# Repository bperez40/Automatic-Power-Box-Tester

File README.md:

# Automatic Power Box Tester
Summer 2022 ITW Vulcan Project

## Firmware Guide
 This guide assumes you're running Windows, however, you can easily do all this on other platforms, but some of the steps will vary slightly, and you probably won't be using anything with a batch script on another platform (unless you really want to).

### Cloning Repo (required)
If you don't have git installed, go ahead and download it from here: https://git-scm.com/
Then, in a command-line shell (On Windows, Command Prompt and PowerShell are installed by default), navigate to wherever you want to store the project and then run:
git clone https://github.com/bperez40/Arduino-Power-Box-Tester

The repository is layed out as follows
```
Automatic-Power-Box-Tester
├───lib
│   ├───Adafruit-GFX-Library
│   ├───Adafruit_BusIO
│   ├───Adafruit_RA8875
│   ├───iodefs
│   ├───PBTCheck
│   ├───PBTGraphics
│   └───PWM
├───main
├───tests
│   ├───ADC_test
│   └───PWM_Out
└───util
    ├───Hardware Design Files
    │   ├───AutoPowerBoxTesterv1.0
    │   │   └───GerberFiles
    │   ├───AutoPowerBoxTesterv1.1
    │   │   └───GerberFiles
    │   └───SparkWireInterfacev1.0
    │       └───GerberFiles
    ├───scripts
    └───images
```
Opening it up, you'll be on the root of the repository.
- main stores the main program
- lib has all the required external and custom libraries for the project
- tests has some basic tests mostly used for debugging and not much else
- util has images used in the readme as well as all the hardware design files for the PCBs

Go ahead and run the update.bat script. This initializes all the submodules, which have dependencies that the firmware uses. Also run this whenever you want to pull the most recent version of the firmware.

### Arduino Setup (required)
We're not quite ready to actually compile and upload firmware to the Arduino yet. We need to install a program to do so. You have a few ways to do this.

#### 1. Using Arduino CLI (recommended)
If you want to use the Arduino CLI to make your own custom configuration, start by downloading the Arduino CLI from Arduino here: https://www.arduino.cc/pro/cli

Extract it in the repository's root and rename the folder it's contained in to .arduino-cli. So, {top-of-repository}/.arduino-cli

Your new file structure will look something like this...
```
Automatic-Power-Box-Tester
├───.arduino-cli
├───lib
│   ├───Adafruit-GFX-Library
│   ├───Adafruit_BusIO
│   ├───Adafruit_RA8875
│   ├───iodefs
│   ├───PBTCheck
│   ├───PBTGraphics
│   └───PWM
├───main
├───tests
│   ├───ADC_test
│   └───PWM_Out
└───util
    ├───Hardware Design Files
    │   ├───AutoPowerBoxTesterv1.0
    │   │   └───GerberFiles
    │   ├───AutoPowerBoxTesterv1.1
    │   │   └───GerberFiles
    │   └───SparkWireInterfacev1.0
    │       └───GerberFiles
    ├───scripts
    └───images
```

The fast way to compile and upload the program is to run the CompileAndUpload.bat script in util.

If you want to compile it manually and play around the the CLI a bit, you can do the following.

To compile, run the following from your root folder:

arduino-cli.exe compile --build-path ./build --libraries ./lib -b Arduino:avr:mega main/main.ino

To compile and upload, you can instead do:

arduino-cli.exe compile --build-path ./build --libraries ./lib -b Arduino:avr:mega -p COM4 -u main/main.ino

Replacing COM4 with whatever your Arduino is actually using. You can figure that out by running:

arduino-cli.exe board list

This is also how you can figure out an Arduino's FQBN.

#### 2. Using Arduino IDE
I haven't set this up on Arduino IDE, but I imagine this is what people are more familar with when using any Arduino platform. If you do this, you'll have to manually add the libraries using the GUI and set up the board type and COM port similar to option 2. If that's done correctly, all you have to do is press the run button and it should work fine.

### Changing the lock screen password (important, but optional)
I recognize that this is incredibly insecure, but it's highly unlikely anyone who would abuse this would come looking here to do so.

To change the lockscreen password, navigate to PBTGraphics.cpp and change the line with...

int actual_passcode[4] = {#, #, #, #}; /*!! SET PASSCODE HERE !!*/

...by setting the # to whatever you want it to be, in the order you want them to be entered. Then build and upload the project to the Arduino.

### Running Python Scripts (optional)
If you don't already have it installed, install from their website: https://www.python.org/

Once Python is installed, open a terminal. 

In the repository's root folder, run python -m venv .venv
.venv is gitignored by default, but if you want to name it something else, change the gitignore to reflect whatever you call it.

VSCode should give a prompt that it has detected a new virtual environment. Confirm the prompt.

Select the proper virtual environment interpreter by opening the command pallette and selecting it using >Python: Select Interpreter

In Windows, run the activate script to use your virtual environment. You could use the
global environment instead, but that's icky:
{wherever-venv-is}\.venv\scripts\activate

If using the debugger, you might need to activate it again in the new terminal that pops up.

If you get the message "Activate.ps1" is not digitally signed, run:
Set-ExecutionPolicy -ExecutionPolicy RemoteSigned -Scope Process

Once the virtual environment is activated, install whatever packages you want using
pip install {package-name}
If you get an error running a python script, chances are you're missing a package. Read the terminal output to see what exactly the error is.

Whenever you're done working in the virtual environment, type deactivate and you'll leave the virtual environment and return to the global environment.

### Logging Arduino output data using PuTTY (optional)
If you want to log the Arduino's output data when it's connected over USB, you can do so using PuTTY (or TeraTerm, or whatever other similar program).

First, install PuTTY from here: https://www.putty.org/

Match all the proper settings in the session tab, such as COM port, baud rate, so on so forth.

In the logging tab, set session logging to "All session output." Name the file whatever you like and configure PuTTY to store putty.log or whatever you want to call it in the util folder of the repository. When you start a session, PuTTY will then create a log in the util folder. You can run the visualizer python script to then visualize the file's output. This is useful for graphing ADC data.

If you want to start PuTTY using a terminal, run the following command:

plink.exe -load {SAVED-PROFILE}

Where the saved profile is one that you've previously set up. If plink.exe isn't found, make sure it's part of your PATH environment.

## Hardware
Hardware design files and assembly instructions can be found in util/HardwareDesignFiles.\
They include the EAGLE board and schematic files, gerber files, BOM, and pick and place for each board.\
You can also view each board on AISLER with the following links.\
[Auto Power Box Tester v1.1 (redirect)](https://aisler.net/p/JCLNWTRR)\
[Spark Wire Interface Board v1.0 (redirect)](https://aisler.net/p/PQONZLWA)\
[Auto Power Box Tester v1.0 (redirect)](https://aisler.net/p/SKLRNZQZ)

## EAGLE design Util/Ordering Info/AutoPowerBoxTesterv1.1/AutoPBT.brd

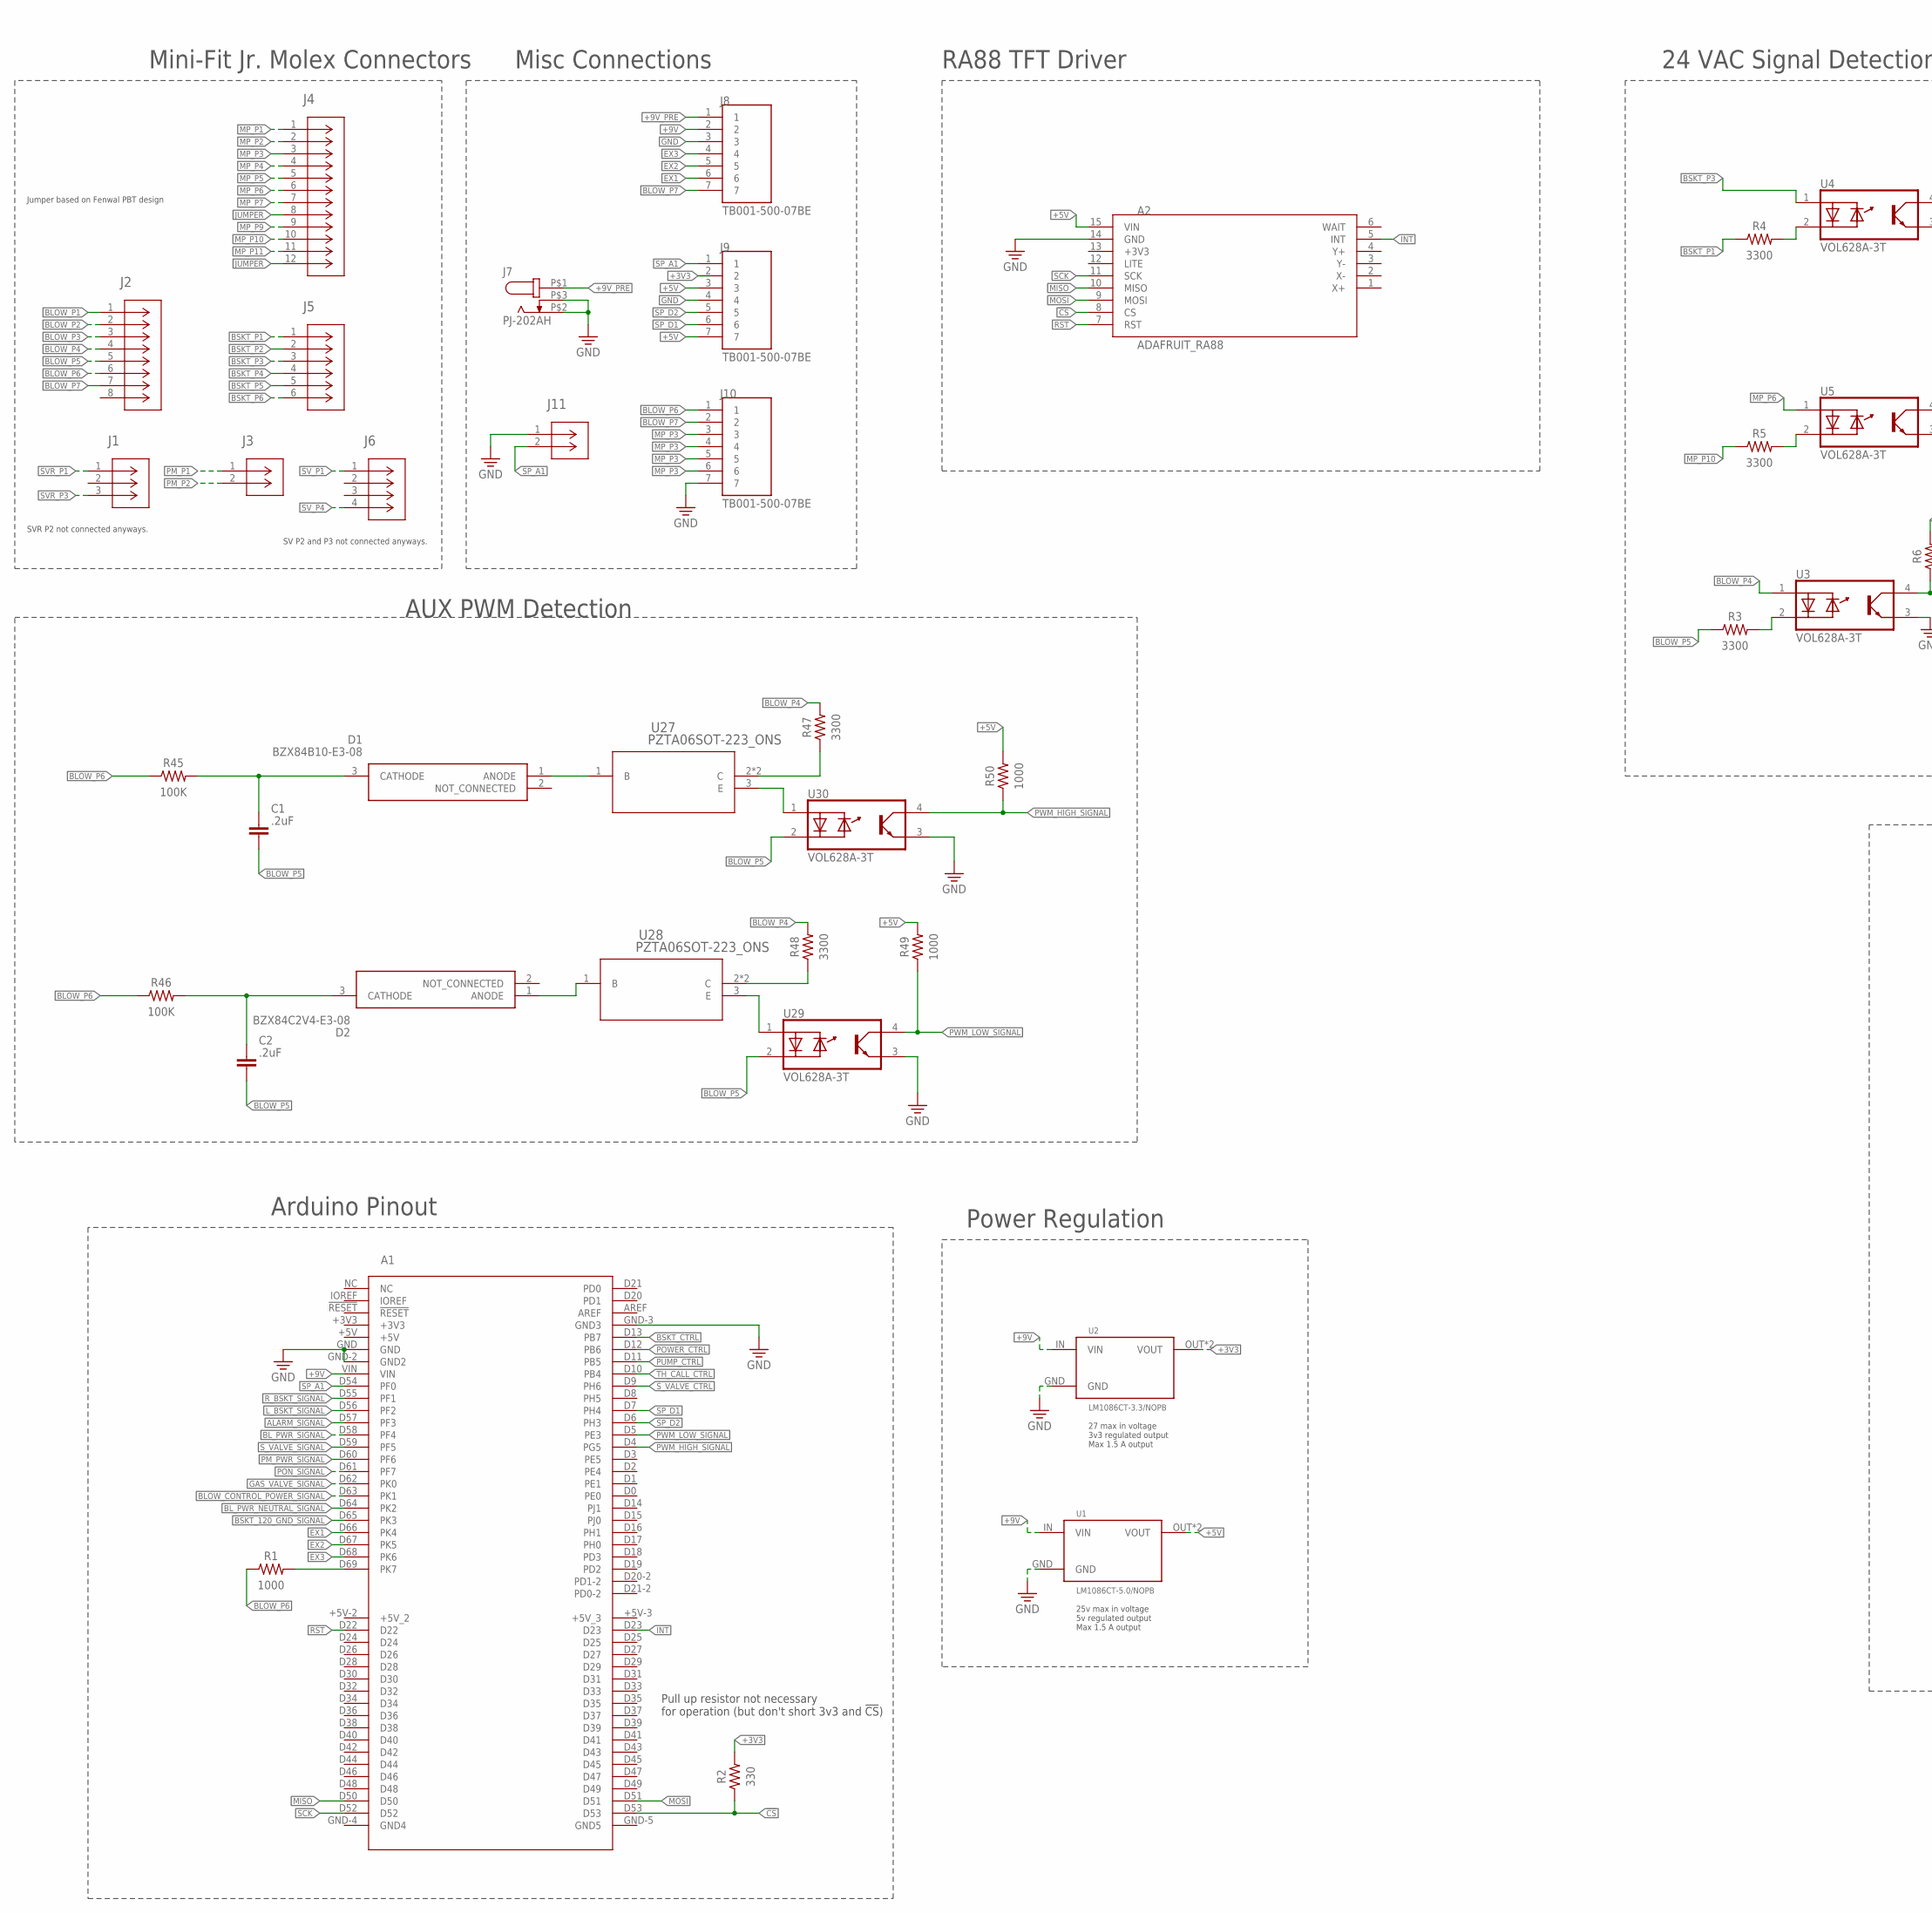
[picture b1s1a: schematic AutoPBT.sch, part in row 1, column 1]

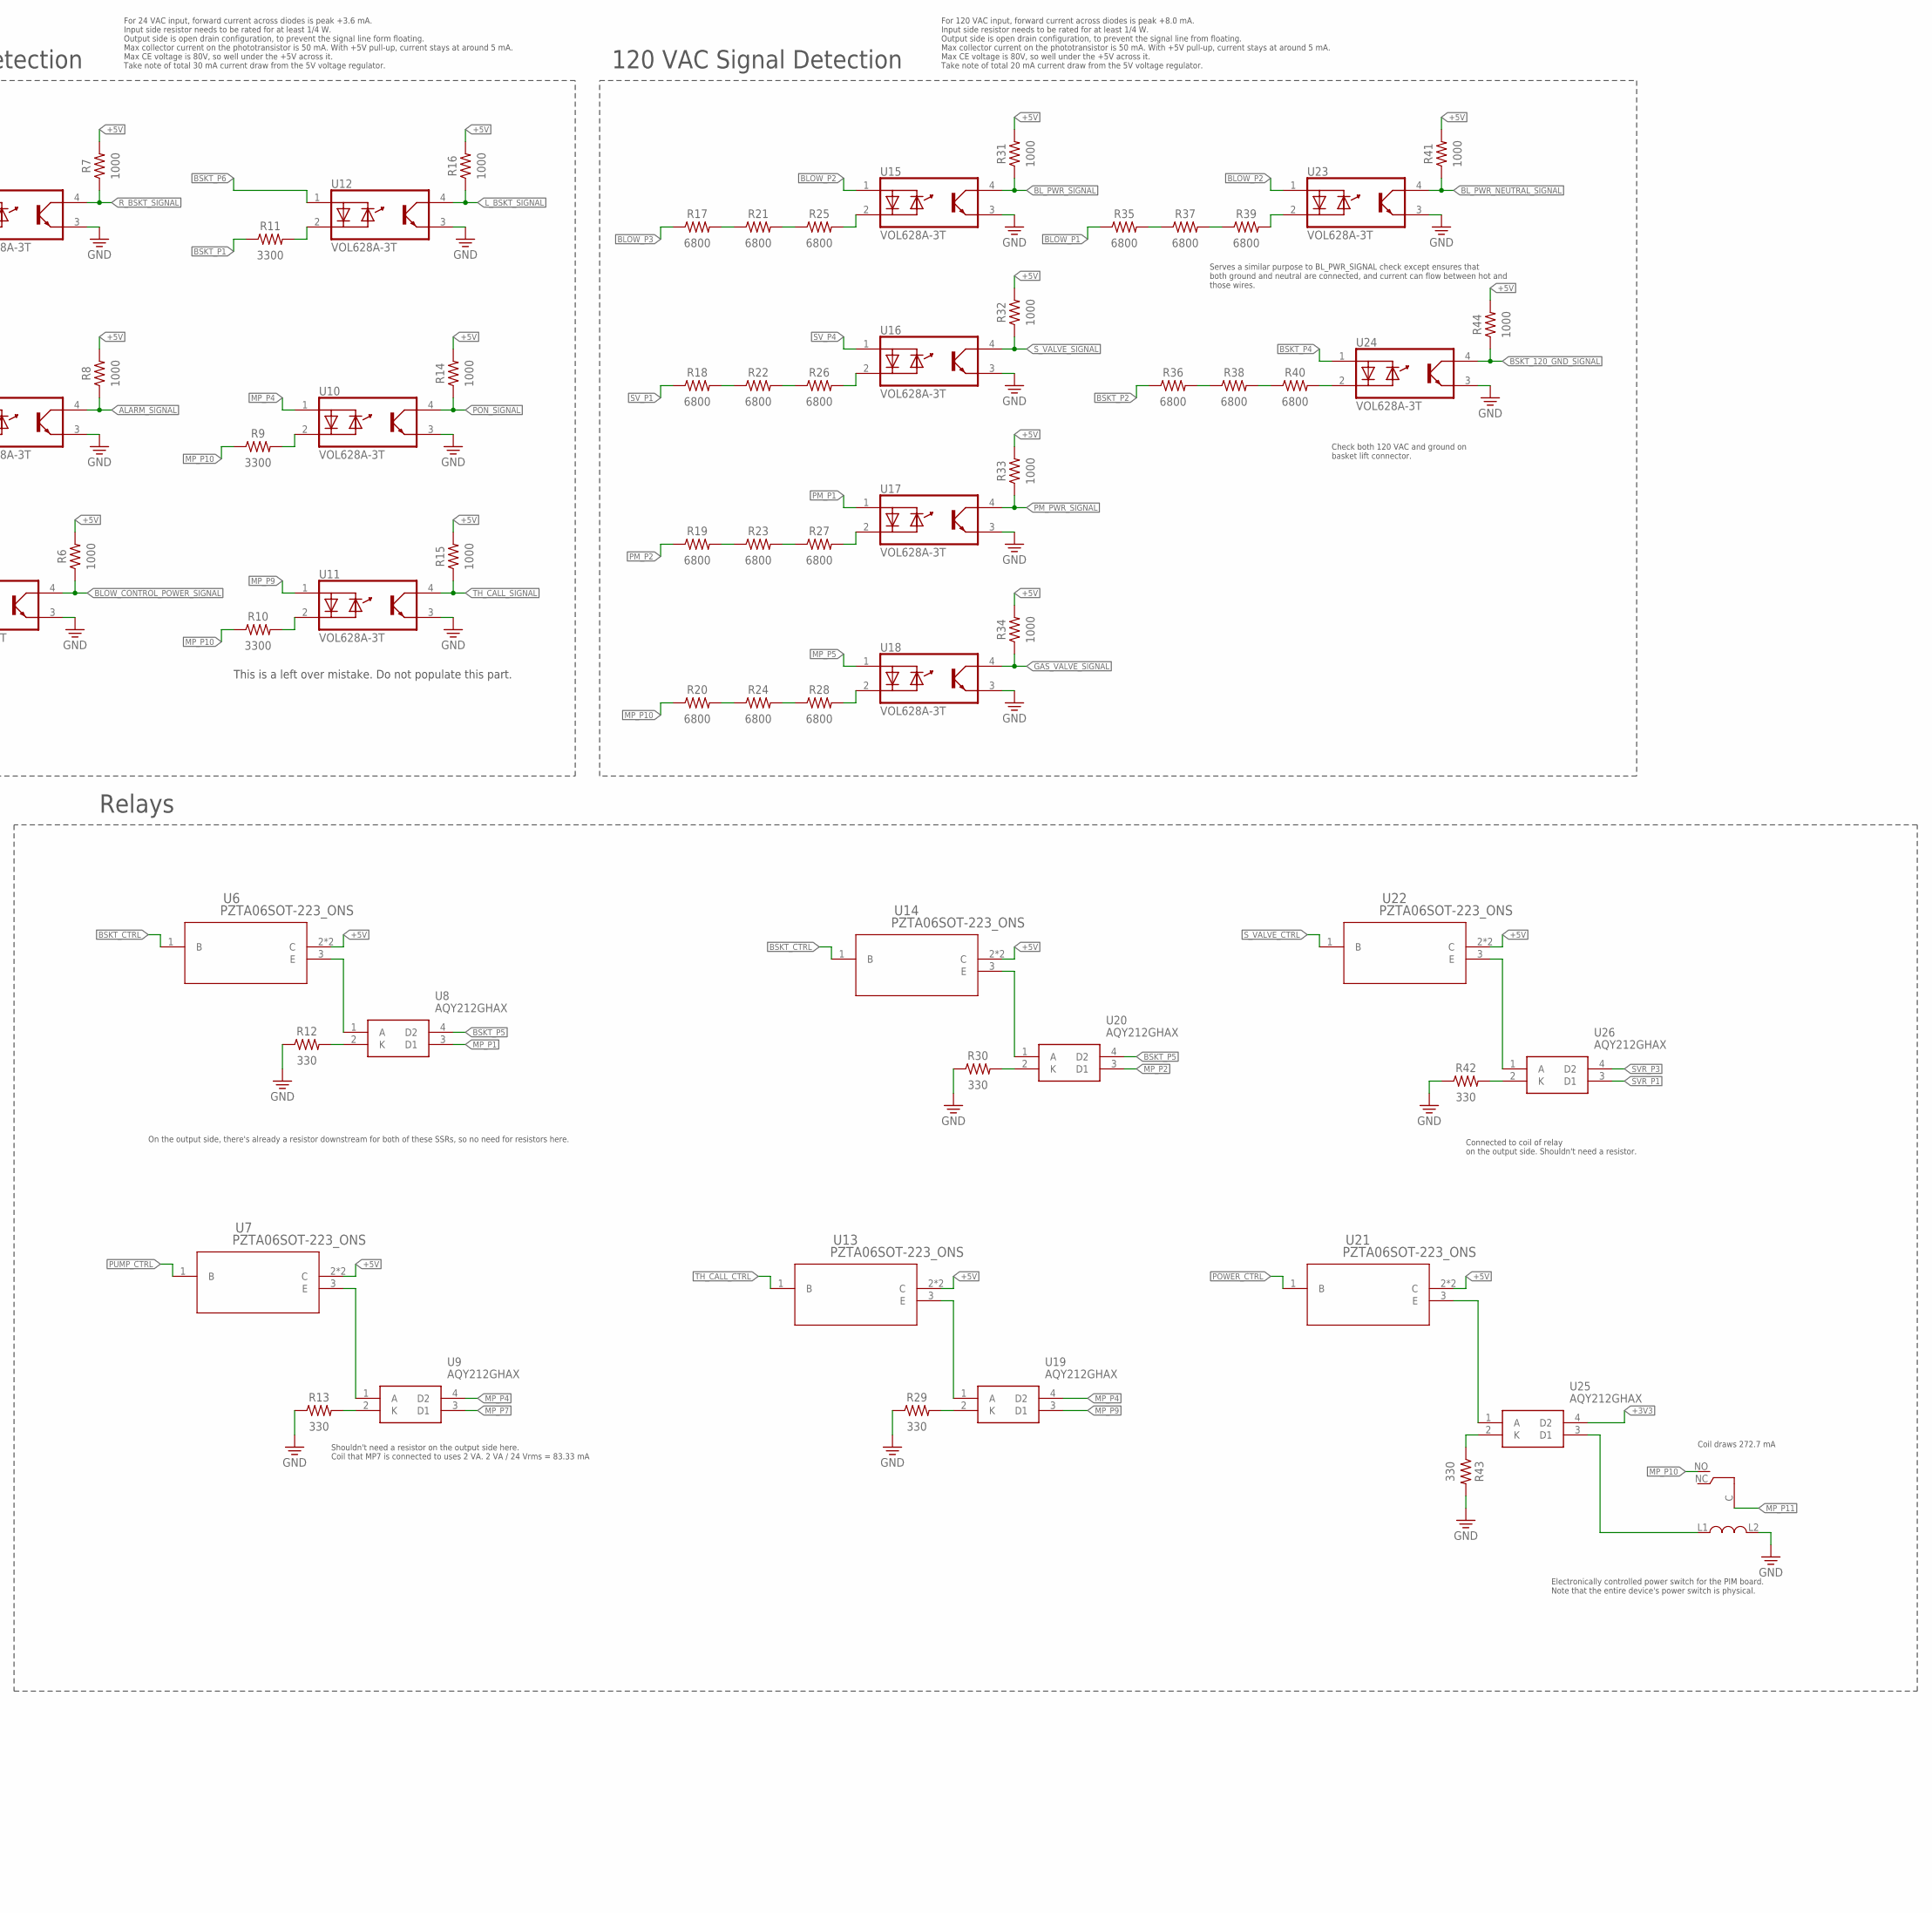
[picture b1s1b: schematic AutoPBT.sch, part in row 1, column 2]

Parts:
A1: ARDUINO2560ARDUINO2560ACTUAL; ARDUINO2560PINS
A2: ADAFRUIT_RA88; RA88
C1, C2: .2uF; CAPC1608X85
D1: BZX84B10-E3-08; SOT95P248X115-3N
D2: BZX84C2V4-E3-08; SOT95P248X115-3N
J1: 39301039CON_39301039; CON_39301039
J2: 39281083CON_39281083; CON_39281083
J3: 39281023CON_39281023; CON_39281023
J4: 39281123CON_39281123; CON_39281123
J5: 39281063CON_39281063; CON_39281063
J6: 39299046CON_39299046; CON_39299046
J7: PJ-202AH; CUI_PJ-202AH
J8, J9, J10: TB001-500-07BE; CUI_TB001-500-07BE
J11: 430450212CON_430450212_MOL; CON_430450212_MOL
K1: J107F1CS203VDC.80
R1, R6, R7, R8, R14, R15, R16, R31, R32, R33, R34, R41, R44, R49, R50: 1000; RESC1608X60
R2, R12, R13, R29, R30, R42, R43: 330; RESC1608X60
R3, R4, R5, R9, R10, R11, R47, R48: 3300; RESC1608X60
R17, R18, R19, R20, R21, R22, R23, R24, R25, R26, R27, R28, R35, R36, R37, R38, R39, R40: 6800; RESC1608X60
R45, R46: 100K; RESC1608X60
U1: LM1086CT-5.0/NOPB; LM1086CT-3.3/NOPB
U2: LM1086CT-3.3/NOPB
U3, U4, U5, U10, U11, U12, U15, U16, U17, U18, U23, U24, U29, U30: VOL628A-3T; SOIC254P1020X230-4N
U6, U7, U13, U14, U21, U22, U27, U28: PZTA06SOT-223_ONS; SOT-223_ONS
U8, U9, U19, U20, U25, U26: AQY212GHAX; SOP254P962X315-4N

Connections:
!CS!: A1.D53, A2.8 (CS), R2.1
+3V3: J9.2, R2.2, U2.OUT (VOUT), U2.OUT2 (VOUT), U25.4 (D2)
+5V: A2.15 (VIN), J9.3, J9.7, R6.2, R7.2, R8.2, R14.2, R15.2, R16.2, R31.2, R32.2, R33.2, R34.2, R41.2, R44.2, R49.2, R50.2, U1.OUT (VOUT), U1.OUT2 (VOUT), U6.2 (C), U6.4 (C), U7.2 (C), U7.4 (C), U13.2 (C), U13.4 (C), U14.2 (C), U14.4 (C), U21.2 (C), U21.4 (C), U22.2 (C), U22.4 (C)
+9V: A1.VIN, J8.2, U1.IN (VIN), U2.IN (VIN)
+9V_PRE: J7.P$1 (1), J8.1
ALARM_SIGNAL: A1.D57 (PF3), R8.1, U5.4 (CO)
BLOW_CONTROL_POWER_SIGNAL: A1.D63 (PK1), R6.1, U3.4 (CO)
BLOW_P1: J2.1, R35.1
BLOW_P2: J2.2, U15.1 (A/C), U23.1 (A/C)
BLOW_P3: J2.3, R17.1
BLOW_P4: J2.4, R47.2, R48.2, U3.1 (A/C)
BLOW_P5: C1.2, C2.2, J2.5, R3.1, U29.2 (C/A), U30.2 (C/A)
BLOW_P6: J2.6, J10.1, R1.1, R45.1, R46.1
BLOW_P7: J2.7, J8.7, J10.2
BL_PWR_NEUTRAL_SIGNAL: A1.D64 (PK2), R41.1, U23.4 (CO)
BL_PWR_SIGNAL: A1.D58 (PF4), R31.1, U15.4 (CO)
BSKT_120_GND_SIGNAL: A1.D65 (PK3), R44.1, U24.4 (CO)
BSKT_CTRL: A1.D13 (PB7), U6.1 (B), U14.1 (B)
BSKT_P1: J5.1, R4.1, R11.1
BSKT_P2: J5.2, R36.1
BSKT_P3: J5.3, U4.1 (A/C)
BSKT_P4: J5.4, U24.1 (A/C)
BSKT_P5: J5.5, U8.4 (D2), U20.4 (D2)
BSKT_P6: J5.6, U12.1 (A/C)
EX1: A1.D66 (PK4), J8.6
EX2: A1.D67 (PK5), J8.5
EX3: A1.D68 (PK6), J8.4
GAS_VALVE_SIGNAL: A1.D62 (PK0), R34.1, U18.4 (CO)
GND: A1.GND, A1.GND-2 (GND2), A1.GND-3 (GND3), A2.14 (GND), J7.P$2 (2), J7.P$3 (3), J8.3, J9.4, J10.7, J11.1, K1.L2 (5), R12.1, R13.1, R29.1, R30.1, R42.1, R43.2, U1.GND, U2.GND, U3.3 (E), U4.3 (E), U5.3 (E), U10.3 (E), U11.3 (E), U12.3 (E), U15.3 (E), U16.3 (E), U17.3 (E), U18.3 (E), U23.3 (E), U24.3 (E), U29.3 (E), U30.3 (E)
INT: A1.D23, A2.5 (INT)
JUMPER: J4.8, J4.12
L_BSKT_SIGNAL: A1.D56 (PF2), R16.1, U12.4 (CO)
MISO: A1.D50, A2.10 (MISO)
MOSI: A1.D51, A2.9 (MOSI)
MP_P1: J4.1, U8.3 (D1)
MP_P2: J4.2, U20.3 (D1)
MP_P3: J4.3, J10.3, J10.4, J10.5, J10.6
MP_P4: J4.4, U9.4 (D2), U10.1 (A/C), U19.4 (D2)
MP_P5: J4.5, U18.1 (A/C)
MP_P6: J4.6, U5.1 (A/C)
MP_P7: J4.7, U9.3 (D1)
MP_P9: J4.9, U11.1 (A/C), U19.3 (D1)
MP_P10: J4.10, K1.NO (1), R5.1, R9.1, R10.1, R20.1
MP_P11: J4.11, K1.C (3)
unnamed: R30.2, U20.2 (K)
unnamed: R29.2, U19.2 (K)
unnamed: R13.2, U9.2 (K)
unnamed: U6.3 (E), U8.1 (A)
unnamed: R42.2, U26.2 (K)
unnamed: R43.1, U25.2 (K)
unnamed: U14.3 (E), U20.1 (A)
unnamed: R39.2, U23.2 (C/A)
unnamed: R37.2, R39.1
unnamed: R35.2, R37.1
unnamed: R40.2, U24.2 (C/A)
unnamed: R38.2, R40.1
unnamed: R36.2, R38.1
unnamed: U22.3 (E), U26.1 (A)
unnamed: U7.3 (E), U9.1 (A)
unnamed: R9.2, U10.2 (C/A)
unnamed: U13.3 (E), U19.1 (A)
unnamed: U21.3 (E), U25.1 (A)
unnamed: R11.2, U12.2 (C/A)
unnamed: C2.1, D2.3 (CATHODE), R46.2
unnamed: R3.2, U3.2 (C/A)
unnamed: R4.2, U4.2 (C/A)
unnamed: D2.1 (ANODE), U28.1 (B)
unnamed: R10.2, U11.2 (C/A)
unnamed: R5.2, U5.2 (C/A)
unnamed: A1.D69 (PK7), R1.2
unnamed: R25.2, U15.2 (C/A)
unnamed: R21.2, R25.1
unnamed: R17.2, R21.1
unnamed: R26.2, U16.2 (C/A)
unnamed: R22.2, R26.1
unnamed: R18.2, R22.1
unnamed: R27.2, U17.2 (C/A)
unnamed: R23.2, R27.1
unnamed: R19.2, R23.1
unnamed: R28.2, U18.2 (C/A)
unnamed: R24.2, R28.1
unnamed: R20.2, R24.1
unnamed: R12.2, U8.2 (K)
unnamed: D1.1 (ANODE), U27.1 (B)
unnamed: C1.1, D1.3 (CATHODE), R45.2
unnamed: U28.3 (E), U29.1 (A/C)
unnamed: U27.3 (E), U30.1 (A/C)
unnamed: R47.1, U27.2 (C), U27.4 (C)
unnamed: R48.1, U28.2 (C), U28.4 (C)
PM_P1: J3.1, U17.1 (A/C)
PM_P2: J3.2, R19.1
PM_PWR_SIGNAL: A1.D60 (PF6), R33.1, U17.4 (CO)
PON_SIGNAL: A1.D61 (PF7), R14.1, U10.4 (CO)
POWER_CTRL: A1.D12 (PB6), U21.1 (B)
PUMP_CTRL: A1.D11 (PB5), U7.1 (B)
PWM_HIGH_SIGNAL: A1.D4 (PG5), R50.1, U30.4 (CO)
PWM_LOW_SIGNAL: A1.D5 (PE3), R49.1, U29.4 (CO)
RELAY_POW: K1.L1 (4), U25.3 (D1)
RST: A1.D22, A2.7 (RST)
R_BSKT_SIGNAL: A1.D55 (PF1), R7.1, U4.4 (CO)
SCK: A1.D52, A2.11 (SCK)
SP_A1: A1.D54 (PF0), J9.1, J11.2
SP_D1: A1.D7 (PH4), J9.6
SP_D2: A1.D6 (PH3), J9.5
SVR_P1: J1.1, U26.3 (D1)
SVR_P3: J1.3, U26.4 (D2)
SV_P1: J6.1, R18.1
SV_P4: J6.4, U16.1 (A/C)
S_VALVE_CTRL: A1.D9 (PH6), U22.1 (B)
S_VALVE_SIGNAL: A1.D59 (PF5), R32.1, U16.4 (CO)
TH_CALL_CTRL: A1.D10 (PB4), U13.1 (B)
TH_CALL_SIGNAL: R15.1, U11.4 (CO)

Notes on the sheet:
Mini-Fit Jr. Molex Connectors
Relays
Misc Connections
120 VAC Signal Detection
24 VAC Signal Detection
RA88 TFT Driver
For 24 VAC input, forward current across diodes is peak +3.6 mA. Input side resistor needs to be rated for at least 1/4 W. Output side is open drain configuration, to prevent the signal line form floating. Max collector current on the phototransistor is 50 mA. With +5V pull-up, current stays at aro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
For 120 VAC input, forward current across diodes is peak +8.0 mA. Input side resistor needs to be rated for at least 1/4 W. Output side is open drain configuration, to prevent the signal line from floating. Max collector current on the phototransistor is 50 mA. With +5V pull-up, current stays at ar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
On the output side, there's already a resistor downstream for both of these SSRs, so no need for resistors here.
Shouldn't need a resistor on the output side here. Coil that MP7 is connected to uses 2 VA. 2 VA / 24 Vrms = 83.33 mA
Connected to coil of relay on the output side. Shouldn't need a resistor.
Coil draws 272.7 mA
Arduino Pinout
Power Regulation
27 max in voltage 3v3 regulated output Max 1.5 A output
25v max in voltage 5v regulated output Max 1.5 A output
Electronically controlled power switch for the PIM board. Note that the entire device's power switch is physical.
SVR P2 not connected anyways.
SV P2 and P3 not connected anyways.
Serves a similar purpose to BL_PWR_SIGNAL check except ensures that both ground and neutral are connected, and current can flow between hot and those wires.
Check both 120 VAC and ground on basket lift connector.
Jumper based on Fenwal PBT design
This is a left over mistake. Do not populate this part.
Pull up resistor not necessary for operation (but don't short 3v3 and !CS!)
AUX PWM Detection

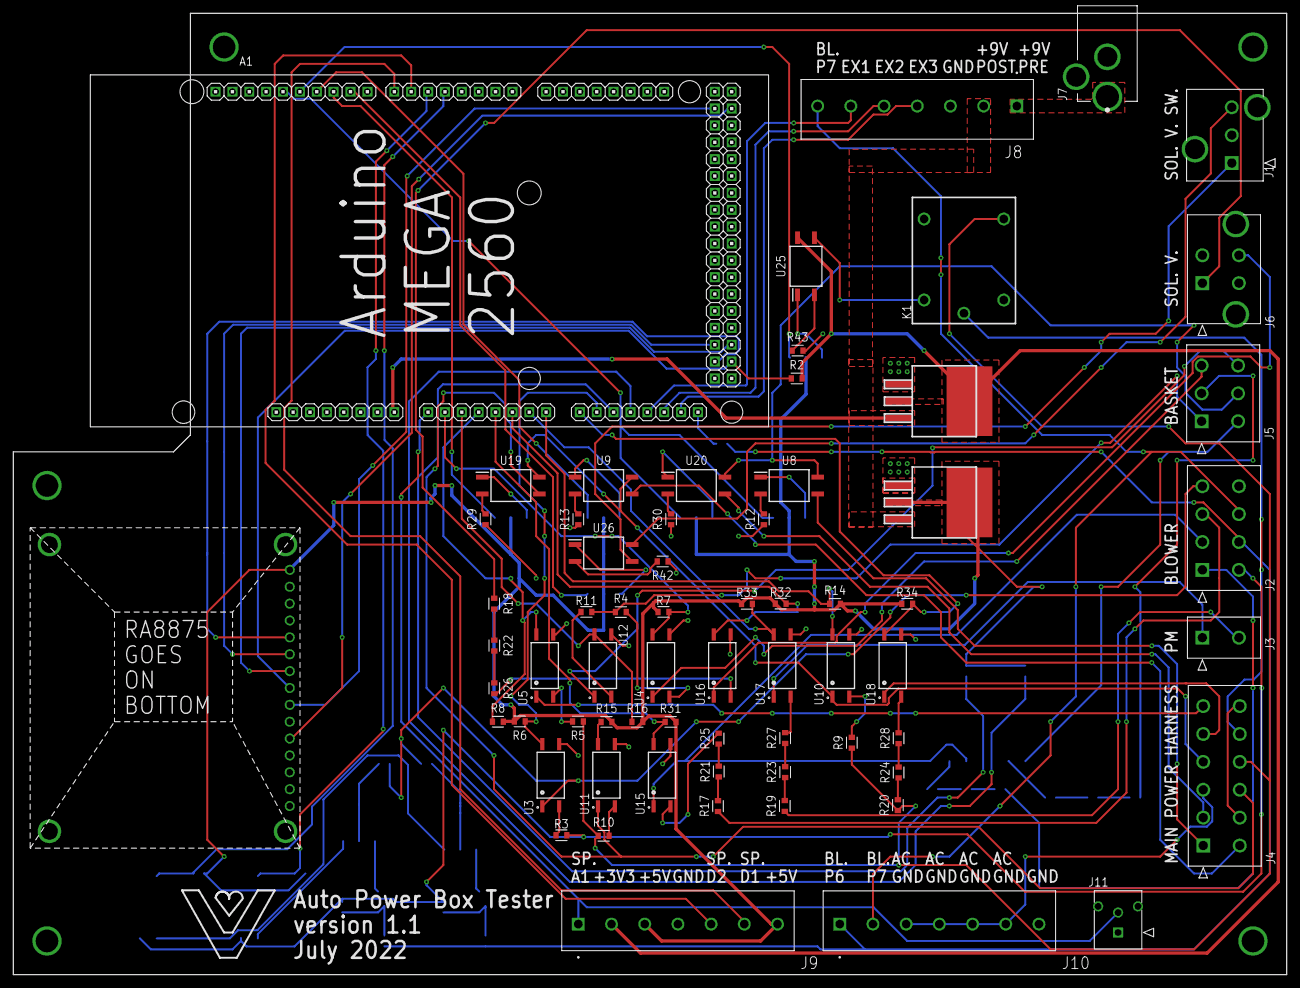
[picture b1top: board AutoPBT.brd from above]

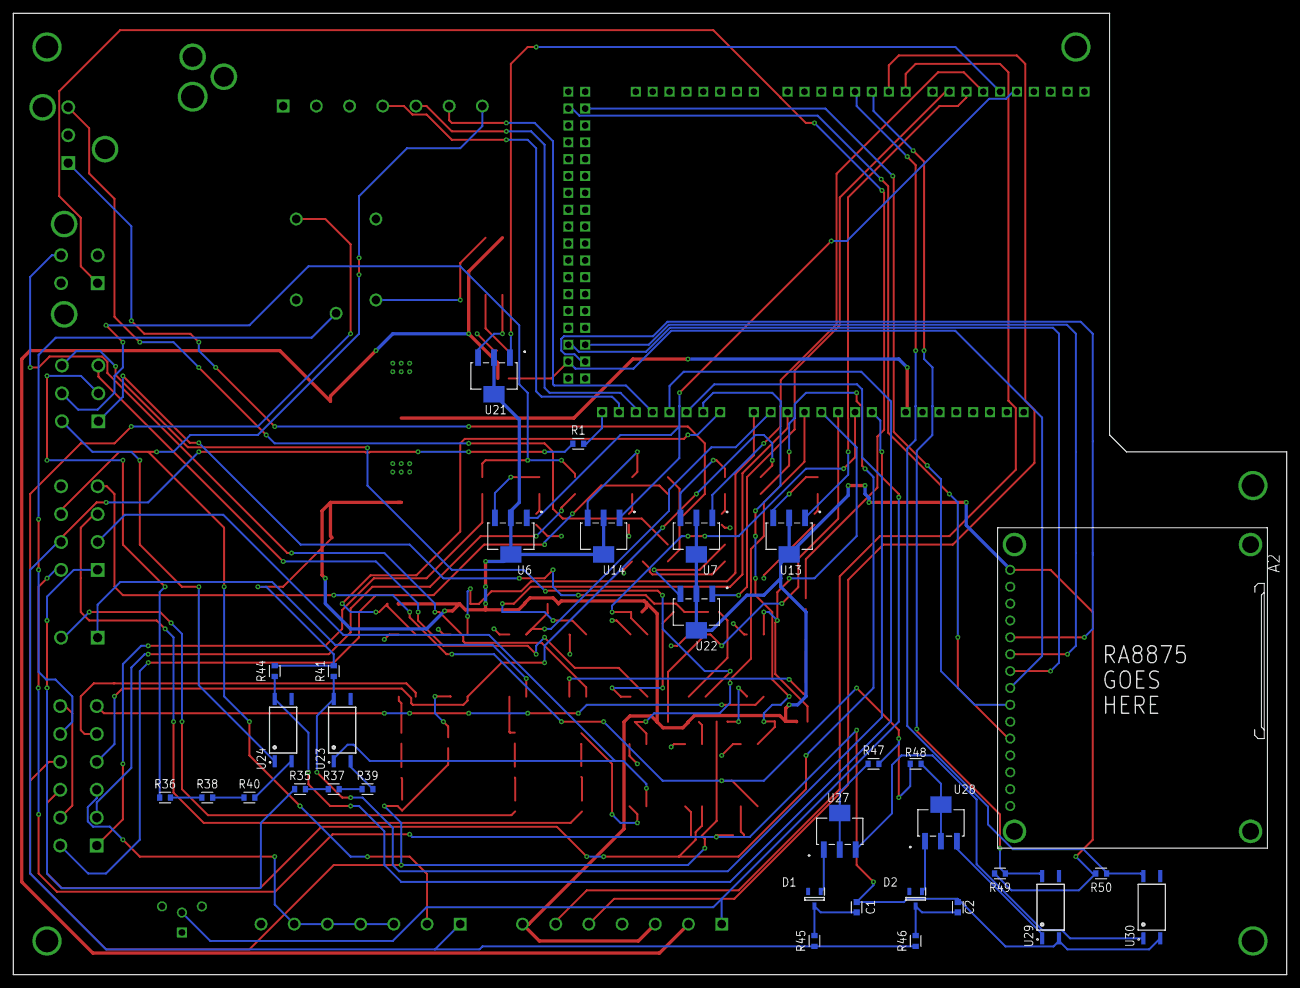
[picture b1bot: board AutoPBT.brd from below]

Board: 2 copper layers, 191.8 x 144.8 mm, 98 parts (32 on the bottom side), 112 nets.

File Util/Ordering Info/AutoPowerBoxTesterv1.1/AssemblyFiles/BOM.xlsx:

Description | Qty | MPN | Designator | Footprint | Additional Comments
1k ohm, 1/4 W, 0603, 1% | 15 | CRGP0603F1K0 | R1, R6, R7, R8, R14, R15, R16, R31, R32, R33, R34, R41, R44, R49, R50 | CHIP-0603(1608-METRIC)
330 ohm, 1/4 W, 0603, 1% | 7 | CRGP0603F330R | R2, R12, R13, R29, R30, R42, R43 | CHIP-0603(1608-METRIC)
3.3k ohm, 1/4 W, 0603, 1% | 8 | CRGP0603F3K3 | R3, R4, R5, R9, R10, R11, R47, R48 | CHIP-0603(1608-METRIC)
6.8k ohm, 1/4 W, 0603, 1% | 18 | CRGP0603F6K8 | R17, R18, R19, R20, R21, R22, R23, R24, R25, R26, R27, R28, R35, R36, R37, R38,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 | CHIP-0603(1608-METRIC)
100k ohm, 2512 | 2 |  | R45, R46 | CHIP-2512
.2uF, 0603 | 2 |  | C1, C2 | CHIP-0603(1608-METRIC)
Mini-Fit Jr. 2 Connections | 1 | 39281023 | J3 | CON_39281023
Mini-Fit Jr. 4 Connections | 1 | 39299046 | J6 | CON_39281043
Mini-Fit Jr. 6 Connections | 1 | 39293066 | J5 | CON_39281063
Mini-Fit Jr. 8 Connections | 1 | 39293083 | J2 | CON_39281083
Mini-Fit Jr. 12 Connections | 1 | 39281123 | J4 | CON_39281123
Mini-Fit Jr. 3 Connections | 1 | 39301039 | J1 | CON_39301039
Micro-Fit 3.0 2 Connections, vertial | 1 | 430450212 | J11 | CON_430450212
Zener Diode, 10V | 1 | BZX84B10-E3-08 | D1 | SOT95P248X115-3N
Zener Diode, 2.4V, 0.35 W, 5% | 1 | BZX84C2V4-E3-08 | D2 | SOT95P248X115-3N
SPST, 3V Relay | 1 | J107F1CS203VDC.80 | K1 | N/A
LM1086CT-3.3/NOPB | 1 | LM1086CT-3.3/NOPB | U2 | TO-220-3
LM1086CT-5.0/NOPB | 1 | LM1086CT-5.0/NOPB | U1 | TO-220-3
9V, 5A, Through Hole Barrel Jack Connector | 1 | PJ-202AH | J7 | PJ-202AH
Terminal Block, 7 Connections, Flathead Screws | 3 | TB001-500-07BE | J8, J9, J10 | TB001-500-07BE
AQY212GHAX | 6 | AQY212GHAX | U8, U9, U19, U20, U25, U26 | SOP254P962X315-4N
TRANS NPN 80V 0.5A SOT223-4 | 8 | PZTA06 | U6, U7, U13, U14, U21, U22, U27, U28 | TO-261-4
Optocoupler, Phototransistor Output, AC/DC Input, Low Input Current | 14 | VOL628A-3T | U3, U4, U5, U10, U11, U12, U15, U16, U17, U18, U23, U24, U29, U30 | SOIC254P1020X230-4N
RA8875 DRIVER BOARD FOR 40P TFT | 1 | 1528-1861-ND | A2 | N/A | Do Not Install
ARDUINO MEGA2560 ATMEGA2560 | 1 | 1050-1018-ND | A1 | N/A | Do Not Install

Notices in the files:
parts and their libraries:
COPYRIGHT: Copyright (C) 2022 Ultra Librarian. All rights reserved.
